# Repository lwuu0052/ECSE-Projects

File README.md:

# ECSE Projects

A collection of my Electrical & Computer Systems Engineering projects from Monash University Malaysia, covering FPGA/Verilog digital design, STM32 embedded systems, analogue circuit design, PCB design, communication systems, MEMS device fabrication, and undergraduate research in visible light communication.

**Author:** Wu Li Min

## Projects

| Project | Area | Tools / Hardware | Highlights |
|---|---|---|---|
| [16-bit x72 Soft-Core Processor](16-bit%20x72%20Soft-Core%20Processor%20report/) | Digital design | Verilog, Quartus Prime, ModelSim, Intel MAX 10 (DE10-Lite) | Bus-based 16-bit processor with 7 instructions, a 4-tick FSM control unit and BCD display; 3,396 self-checking testbench cases |
| [Dual-STM32 Audio Acquisition System](Dual-STM32%20Audio%20Acquisition%20System%20slide/) | Embedded systems | STM32L432KC, STM32CubeIDE, C, Python | 44.1 kHz / 12-bit audio sampling over SPI, ultrasonic trigger, UART at 921600 bps, Python CLI exporting WAV/CSV/PNG |
| [True-RMS-to-DC Converter](TRUE-RMS-TO-DC%20CONVERTER/) | Analogue design | LTspice, TL084/TL974, 2N3904, Analog Discovery 3 | Discrete log–antilog converter; all 13 test cases within ±1 % (mean error 0.46 %), DC to 20 kHz |
| [PIR Motion-Activated LED Fader PCB](PCB_Project/) | PCB design | KiCad 10 | Two-layer board with PIR interface, adjustable RC fade-in/fade-out timing and MOSFET LED driver |
| [CDMA with Walsh–Hadamard Codes](CDMA_project/) | Communications | MATLAB | Two-user BPSK CDMA simulation: BER vs Eb/N0, near–far problem, timing-offset leakage |
| [One-Port SAW Resonator](One-Port%20SAW%20Resonator/) | MEMS / sensors | Photolithography, FESEM, AFM, NanoVNA, ESP32-C3, Python | Fabricated 129.6 MHz LiNbO₃ resonator; TCF of −48 ± 7 ppm/°C measured in a PI-controlled thermal chamber |
| [UROP – Visible Light Communication (SPI link)](UROP%20Project%20-%20Visible%20Light%20Communication%20Systems%20with%20Microcontrollers%20or%20FPGAs/) | Research | Verilog, Quartus, Teensy 4.1, PlatformIO (C++), DE2-115 | Replaced the UART PC–FPGA link with SPI; up to ~4.57 Mbps within a packet |

## Repository layout

```
.
├── 16-bit x72 Soft-Core Processor report/   Verilog sources, Quartus project, report (PDF)
├── CDMA_project/                            MATLAB simulation script, report (PDF)
├── Dual-STM32 Audio Acquisition System slide/
│   └── code/                                Sampling STM, Processing STM, Python + C CLI
├── One-Port SAW Resonator/                  Project report (PDF)
├── PCB_Project/PIR_Sensor/                  KiCad project, schematic (PDF), layout render
├── TRUE-RMS-TO-DC CONVERTER/                Project report (PDF)
└── UROP Project - Visible Light .../        FPGA + Teensy SPI code for both master/slave setups
```

Each project folder has its own README with an overview, implementation details, results and instructions for opening or running the work.

## Skills demonstrated

- **Digital design:** RTL design in Verilog, FSMs, datapath/control-unit design, self-checking testbenches, timing and resource analysis in Quartus
- **Embedded systems:** STM32 HAL/LL drivers, ADC, timers, DMA, SPI, UART, Teensy/Arduino, PlatformIO
- **Analogue electronics:** op-amp circuits, translinear log–antilog computation, precision rectifiers, calibration, LTspice simulation
- **PCB design:** schematic capture and two-layer layout in KiCad
- **Signal processing & communications:** CDMA, BPSK, BER analysis, Monte Carlo simulation in MATLAB
- **Microfabrication & characterisation:** thermal evaporation, photolithography, FESEM/AFM, VNA measurements
- **Software:** C, C++, Python (serial acquisition, data logging, automation), MATLAB
- **Teamwork:** most projects were completed in teams; collaborators are credited in each project's README

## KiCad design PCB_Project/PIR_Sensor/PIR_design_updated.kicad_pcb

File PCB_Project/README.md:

# PIR Motion-Activated LED Fader PCB

A two-layer PCB designed in KiCad 10. It turns an LED on when a PIR motion sensor detects movement, with adjustable fade-in and fade-out times.

## Circuit

| Section | Description |
|---|---|
| Power input | 5 V through J2, with 100 µF bulk and 100 nF decoupling capacitors |
| PIR interface | 3-pin headers (VCC / OUT / GND) for the PIR sensor module |
| Fade timing control | `PIR_out` charges C3 (47 µF) through D1 and potentiometer R2 (fade-in), and discharges it through D3 and potentiometer R3 (fade-out). R1 (1 MΩ) provides a bleed path |
| LED driver | The C3 voltage drives the gate of an IRFZ44N N-MOSFET, which controls the LED (R4 = 330 Ω, R5 = 220 Ω) |

Because the two 1N4148 diodes face opposite directions, charging and discharging take separate paths, so the fade-in and fade-out times can be set independently with the two potentiometers.

## Board

- Two copper layers (F.Cu / B.Cu), all through-hole components
- Four M3 mounting holes (H1–H4)

## Files

| Path | Contents |
|---|---|
| `PIR_Sensor/PIR_design_updated.kicad_pro` | KiCad project |
| `PIR_Sensor/PIR_design_updated.kicad_sch` | Schematic |
| `PIR_Sensor/PIR_design_updated.kicad_pcb` | PCB layout |
| `PIR_Sensor/Schematic.pdf` | Exported schematic |
| `PIR_Sensor/Layout.png` | 3D render of the board |

## How to open

Open `PIR_Sensor/PIR_design_updated.kicad_pro` in **KiCad 10** or later. The files use the KiCad 10 format and may not open in older versions.

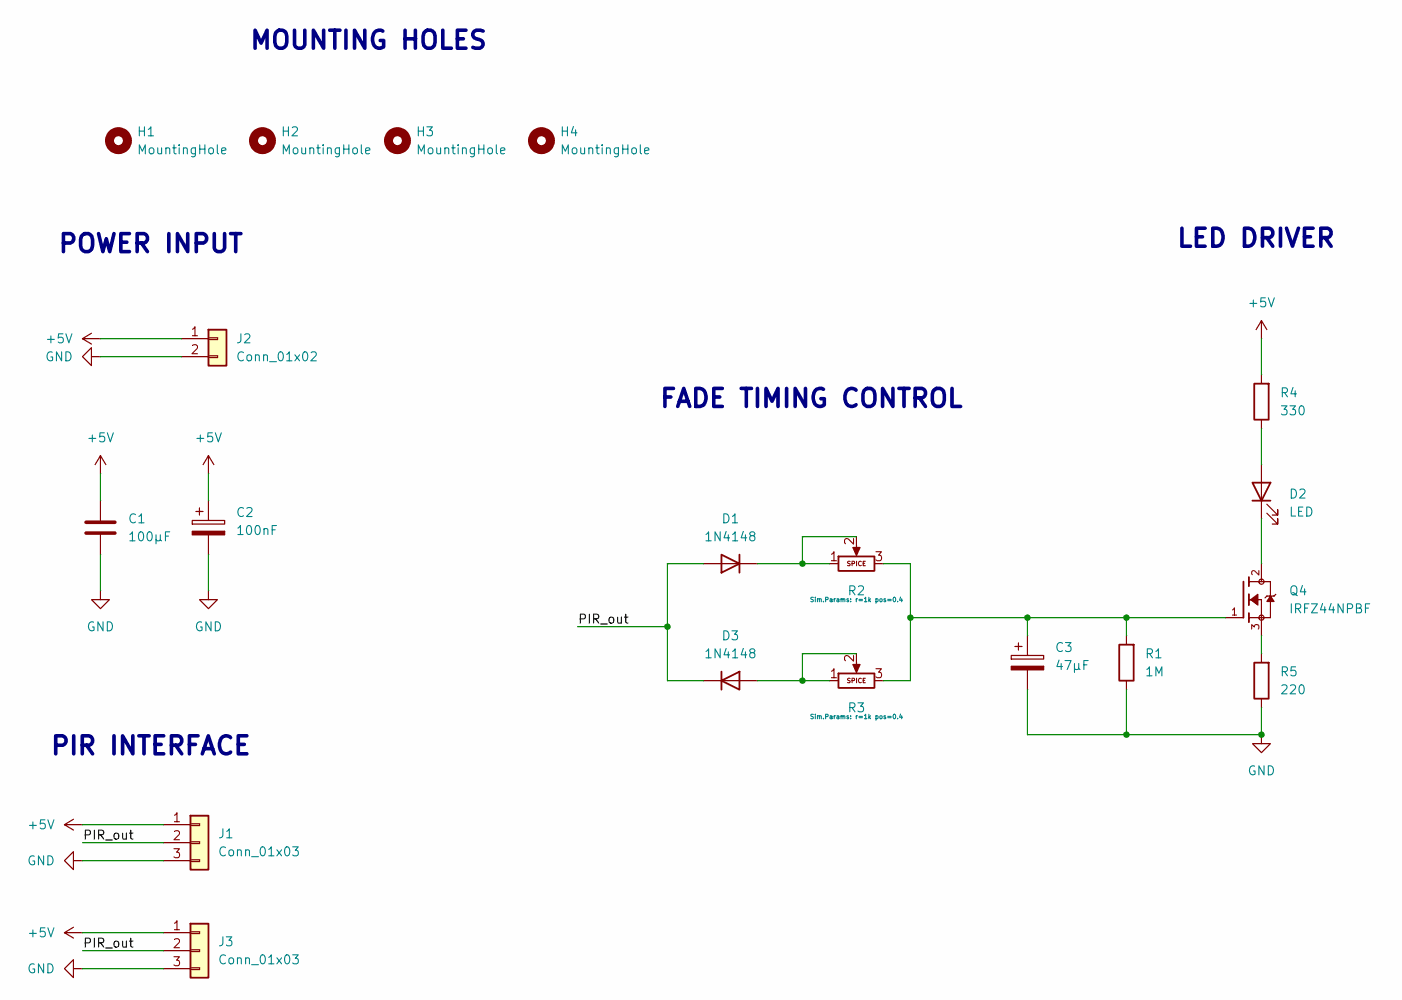
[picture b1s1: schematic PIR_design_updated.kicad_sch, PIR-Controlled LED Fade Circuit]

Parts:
C1: 100µF; CP_Radial_D6.3mm_P2.50mm
C2: 100nF; C_Disc_D5.0mm_W2.5mm_P2.50mm
C3: 47µF; CP_Radial_D6.3mm_P2.50mm
D1, D3: 1N4148; D_DO-35_SOD27_P7.62mm_Horizontal
D2: LED; LED_D5.0mm
H1, H2, H3, H4: MountingHole; MountingHole_3.2mm_M3
J1: Conn_01x03; HC-SR501
J2: Conn_01x02; PinHeader_1x02_P2.54mm_Vertical
J3: Conn_01x03; PinHeader_1x03_P2.54mm_Vertical
Q4: IRFZ44NPBF; TO-220-3_Vertical; PARTREV 09/21/10; DigiKey_Part_Number IRFZ44NPBF-ND
R1: 1M; R_Axial_DIN0207_L6.3mm_D2.5mm_P7.62mm_Horizontal
R2, R3: 100k; Potentiometer_Bourns_3296W_Vertical
R4: 330; R_Axial_DIN0207_L6.3mm_D2.5mm_P7.62mm_Horizontal
R5: 220; R_Axial_DIN0207_L6.3mm_D2.5mm_P7.62mm_Horizontal

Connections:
+5V: C1.1, C2.1, J1.1, J2.1, J3.1, R4.2
/PIR_out: D1.2 (A), D3.1 (K), J1.2, J3.2
GND: C1.2, C2.2, C3.2, J1.3, J2.2, J3.3, R1.1, R5.1
unnamed: C3.1, Q4.1, R1.2, R2.3, R3.3
unnamed: D1.1 (K), R2.1, R2.2
unnamed: D2.2 (A), R4.1
unnamed: D2.1 (K), Q4.2
unnamed: D3.2 (A), R3.1, R3.2
unnamed: Q4.3, R5.2

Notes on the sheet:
POWER INPUT
MOUNTING HOLES
LED DRIVER
FADE TIMING CONTROL
PIR INTERFACE

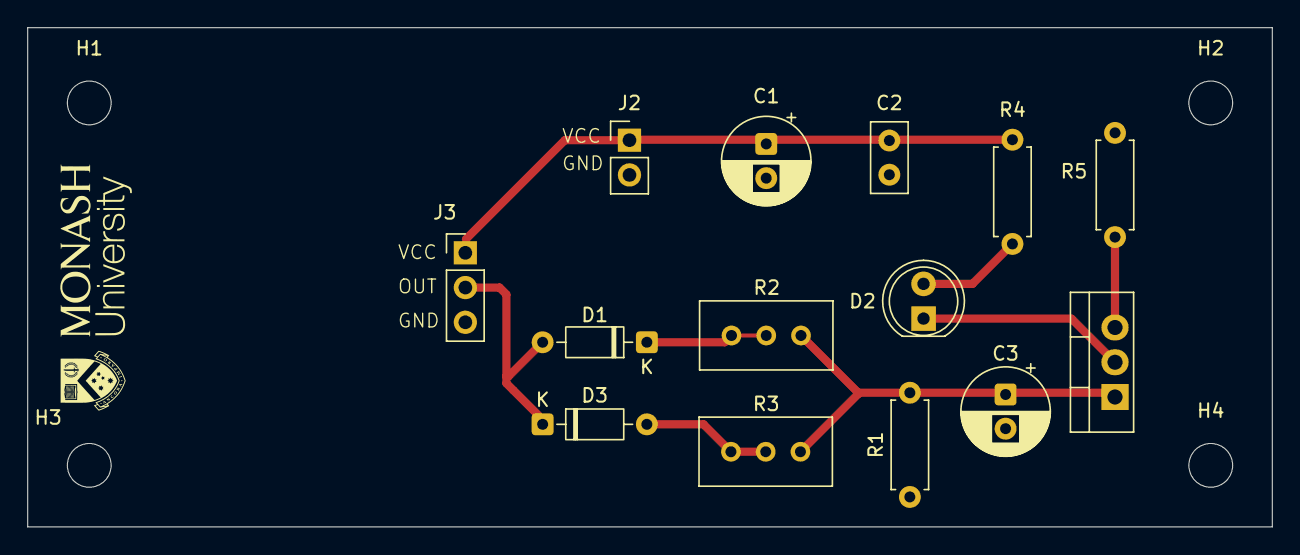
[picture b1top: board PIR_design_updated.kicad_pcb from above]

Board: 2 copper layers, 91.0 x 36.5 mm, 18 parts (0 on the bottom side), 9 nets.
